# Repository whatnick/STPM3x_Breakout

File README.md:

# STPM3x Energy Metering Breakouts

Open-hardware development boards for the STMicroelectronics STPM32, STPM33,
and STPM34 energy-metering ASIC family.

The STPM3x devices combine precision analog conversion with on-chip
calculation of voltage, current, power, energy, and power-quality events. They
support current transformers, shunts, and Rogowski coils, with SPI or UART
host communication and CRC-protected data transfers.

This repository develops a consistent breakout family around all three channel
configurations:

| Board | Measurement channels | Best fit |
|---|---|---|
| **STPM32 Breakout** | 1 voltage + 1 current | Single-phase meters, smart appliances, and compact sensor development |
| **STPM33 Breakout** | 1 voltage + 2 current | Phase/neutral monitoring, tamper detection, and dual-current experiments |
| **STPM34 Breakout** | 2 voltage + 2 current | Split-phase systems, two independent circuits, and two-phase monitoring |

The STPM34 is the most capable member of this family, but it is not a complete
three-phase meter by itself. Applications requiring three simultaneous voltage
and current phases are better served by devices such as the ADE9000 or
ATM90E36.

## Place in the Whatnick ecosystem

The Whatnick energy-monitoring ecosystem includes breakout boards and drivers
for several metering architectures:

- **ATM90E26** for established single-phase SPI metering.
- **ATM90E32/ATM90E36** for three-phase monitoring.
- **ADE7763 and ADE7816** for Analog Devices single- and multi-channel designs.
- **ADE9000** for advanced polyphase metering and power-quality work.
- **CS5464 and CS5490** for Cirrus Logic single-phase applications.
- **MCP39F511 and MCP39F521** for Microchip calculation-engine devices.
- **V9203 and V93xx** for additional polyphase and single-phase platforms.
- **STPM3x** for a scalable STMicroelectronics family using a common register
  model across single-, dual-current, and dual-channel applications.

The aim is not only to expose IC pins. Each breakout should provide a known
hardware platform for driver development, calibration tools, sensor-interface
experiments, waveform analysis, and comparison between metering ASIC families.

## Intended software ecosystem

The three boards are intended to share one transport-independent STPM3x driver
core with device-specific channel capabilities layered on top. Planned software
support includes:

- Register definitions and typed configuration helpers.
- SPI and UART transports.
- CRC generation and checking.
- RMS, power, energy, event, and status access.
- Calibration and register-dump tools.
- Arduino and Python/MicroPython-facing APIs.
- Examples for CT, shunt, and Rogowski-coil measurements.

Keeping a common API across STPM32, STPM33, and STPM34 will allow applications
to move between board variants without maintaining three unrelated drivers.

## Hardware philosophy

These boards are intended as accessible bench-development platforms:

- Clearly separated analog sensor and digital host interfaces.
- Exposed pulse, interrupt, synchronization, clock, and enable signals.
- Space for channel-specific burden, divider, protection, and filtering
  networks.
- 3.3 V host compatibility.
- Compact breadboard modules or larger bench boards according to channel count.
- Readable safety labels and accessible test points.
- Open KiCad 10 source and project-local STPM3x symbols.

The STPM32 variant implements a complete compact front end for a
100 A:50 mA current-output CT and an isolated 9 VAC transformer secondary. It
uses a single 1x12 breadboard header, underside test pads, separate analog and
digital ground pours, and no field-wiring connectors. The STPM33 variant is
also complete, using the same isolated 9 VAC input with two 100 A:50 mA CT
channels, a 1x14 development header, five underside test pads, and a 55 x 40 mm
bench-board envelope. The STPM34 variant is complete on a 75 x 50 mm bench
board with two isolated 9 VAC channels, two 100 A:50 mA CT channels, separate
analog and host headers, and three underside test pads.

## Repository contents

- [`hardware/STPM32_Breakout`](hardware/STPM32_Breakout) - single voltage and
  current channel.
- [`hardware/STPM33_Breakout`](hardware/STPM33_Breakout) - single voltage and
  dual current channels.
- [`hardware/STPM34_Breakout`](hardware/STPM34_Breakout) - dual voltage and
  current channels.
- [`symbols/STPM3x.kicad_sym`](symbols/STPM3x.kicad_sym) - project-local,
  datasheet-verified symbols.
- [`docs/pin-map.md`](docs/pin-map.md) - family pin and package comparison.
- [`docs/design-requirements.md`](docs/design-requirements.md) - shared
  electrical, mechanical, and safety requirements.

## Safety

These are development boards, not certified energy meters. They must not be
connected directly to hazardous voltages without correctly rated isolation,
protection, fusing, spacing, enclosure, and appropriate electrical-safety
practices.

## License

Hardware design files are released under the
[TAPR Open Hardware License 1.0](LICENSE).

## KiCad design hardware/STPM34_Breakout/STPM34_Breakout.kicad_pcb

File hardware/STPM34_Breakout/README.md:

# STPM34 Breakout

KiCad 10 open-hardware breakout for the STMicroelectronics STPM34 metering
ASIC. It measures two isolated voltage channels and two current-transformer
channels for split-phase, dual-circuit, and two-phase development.

## Front end

- Supply: 3.3 V.
- Voltage inputs: two isolated 9 VAC transformer secondaries.
- Current inputs: two 100 A:50 mA CTs.
- Current burdens: 2.4 ohm differential, giving 120 mV RMS at 100 A.
- Current filters: 100 ohm series resistors and 330 nF capacitors.
- Voltage dividers: symmetric 200 kohm / 2.49 kohm per channel.
- Voltage filters: 1 kohm series resistors and 33 nF capacitors.
- Clock: 16 MHz crystal.
- Grounding: separate GNDA and DGND pours joined through NT1. NT1 is a copper
  net tie; no component is fitted there.

This is not an isolated mains-input board. Connect only isolated low-voltage
sources and follow applicable electrical-safety practices.

## Headers

J1 carries the analog inputs:

| Pin | Signal | Pin | Signal |
|---:|---|---:|---|
| 1 | V1AC_P | 5 | CT1_P |
| 2 | V1AC_N | 6 | CT1_N |
| 3 | V2AC_P | 7 | CT2_P |
| 4 | V2AC_N | 8 | CT2_N |

J2 carries power and the host interface:

| Pin | Signal | Pin | Signal |
|---:|---|---:|---|
| 1 | +3V3 | 6 | MISO/TXD |
| 2 | DGND | 7 | SYN |
| 3 | SCS | 8 | EN |
| 4 | SCL | 9 | INT1 |
| 5 | MOSI/RXD | 10 | INT2 |

Underside pads expose LED1, LED2, and CLKOUT/ZCR.

## SPI/UART selector

STPM34 supports SPI or UART, not I2C. SJ1 biases SCS through R14 at power-up:

- Pads 1-2 are closed by default, selecting SPI with a DGND bias.
- For UART, cut pads 1-2 and bridge pads 2-3 to bias SCS to +3V3.
- Press SW1 after changing SJ1 so EN is asserted low and the interface mode is
  sampled again.

## Rebuilding

Run the scripts from the repository root:

```powershell
python .\scripts\build_stpm34_schematic.py
python .\scripts\apply_stpm34_bom.py
& "C:\Program Files\KiCad\10.0\bin\python.exe" .\scripts\build_stpm34_pcb.py
```

Routing uses Freerouting with Java 25:

```powershell
$env:JAVA25 = "C:\Program Files\Eclipse Adoptium\jre-25.0.4.101-hotspot\bin\java.exe"
$env:FREEROUTING_JAR = "C:\path\to\freerouting-2.4.1.jar"
& "C:\Program Files\KiCad\10.0\bin\python.exe" .\scripts\route_stpm34.py
& "C:\Program Files\KiCad\10.0\bin\python.exe" .\scripts\finalize_stpm34_pcb.py
```

The checked-in routed PCB is the production source. Reconstruction scripts
capture the electrical design, 75 x 50 mm rounded envelope, placement,
routing workflow, ground pours, markings, and project-local 3D/logo assets.

## Manufacturing outputs

```powershell
python .\scripts\apply_stpm34_bom.py
python .\scripts\render_stpm34.py
python .\scripts\generate_stpm34_gerbers.py
```

The Elecrow BOM is written to `manufacturing`. Gerbers, separate PTH/NPTH
drills, Gerber job data, front/rear position CSVs, and the upload ZIP are
written to `gerber`. The BOM contains 17 grouped unique parts and 44 fitted
components.

## Breadboard bench scene

The FreeCAD and Blender scene illustrates a safe low-voltage demonstration:
an isolated 9 VAC barrel adapter feeds the voltage input and a 9 VAC lamp,
while a YHDC current-transformer clamp surrounds one lamp conductor and
connects through a stereo-jack breakout. The composition is an original
render inspired by common Whatnick bench practice and the supplied Tindie
reference photograph; it is not a literal reconstruction of that photograph.

Generate the editable FreeCAD model, intermediate STEP/OBJ geometry, Blender
scene, and final PNG from the repository root:

```powershell
& "C:\Program Files\FreeCAD 0.19\bin\FreeCADCmd.exe" .\scripts\build_stpm34_bench_freecad.py
& "C:\Program Files\Blender Foundation\Blender 5.2\blender.exe" --background --python .\scripts\render_stpm34_bench_blender.py
```

The checked-in deliverables are the `.FCStd`, `.blend`, and `.png` files.
Intermediate STEP and OBJ exports are regenerated locally and ignored by Git.

**Safety:** the scene represents an isolated 9 VAC test circuit only. Never
connect mains voltage directly to a breadboard, the STPM34 analog header, or
the rendered barrel/stereo breakout arrangement.

## Validation

KiCad 10 ERC and DRC are mandatory before fabrication export. The Gerber
generator enforces zero ERC/DRC violations and zero unconnected items before
creating the package.

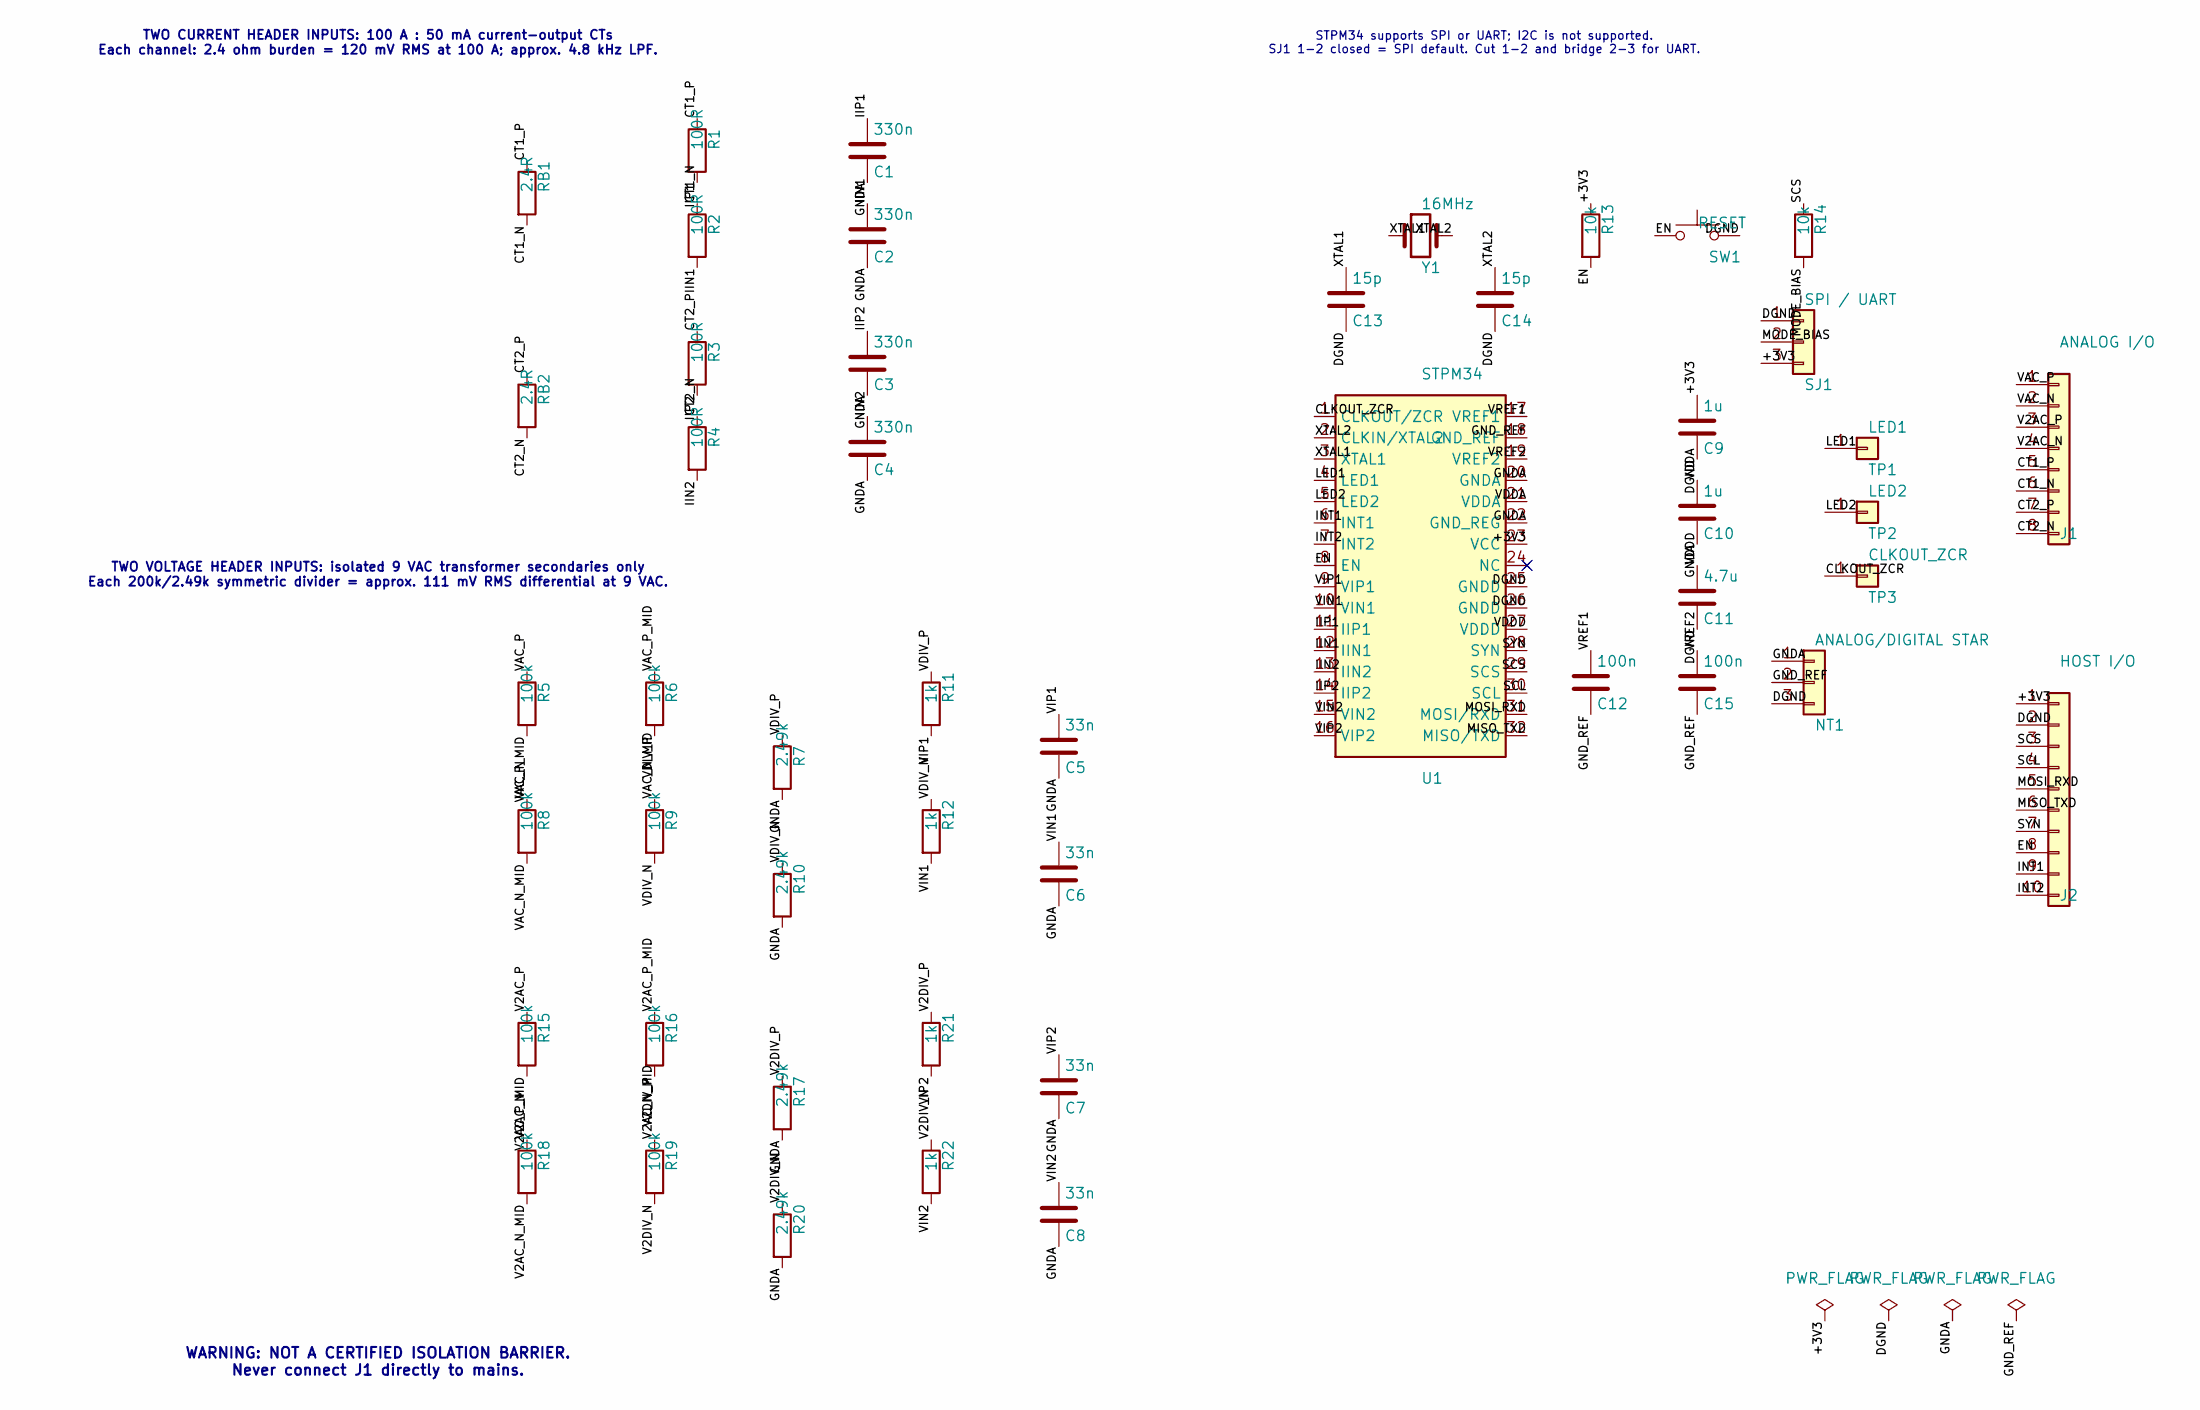
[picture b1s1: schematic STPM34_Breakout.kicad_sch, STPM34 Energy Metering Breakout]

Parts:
C1, C2, C3, C4: 330n; C_0603_1608Metric; MPN TCC0603X7R334K500CT; LCSC C282682
C5, C6, C7, C8: 33n; C_0603_1608Metric; MPN CL10B333KB8NNNC; LCSC C21117
C9, C10: 1u; C_0805_2012Metric; MPN CL21B105KAFNNNE; LCSC C116352
C11: 4.7u; C_0805_2012Metric; MPN CL21A475KOFNNNG; LCSC C16194928
C12, C15: 100n; C_0603_1608Metric; MPN CL10B104KB8NNNC; LCSC C1591
C13, C14: 15p; C_0603_1608Metric; MPN CL10C150JB8NNNC; LCSC C1644
J1: ANALOG I/O; PinHeader_1x08_P2.54mm_Vertical; MPN PZ254V-11-08P; LCSC C492407
J2: HOST I/O; PinHeader_1x10_P2.54mm_Vertical; MPN PZ254V-11-10P; LCSC C492409
NT1: ANALOG/DIGITAL STAR; NetTie-3_SMD_Pad0.5mm
R1, R2, R3, R4: 100R; R_0603_1608Metric; MPN RC0603FR-07100RL; LCSC C105588
R5, R6, R8, R9, R15, R16, R18, R19: 100k; R_0603_1608Metric; MPN RT0603BRD07100KL; LCSC C122538
R7, R10, R17, R20: 2.49k; R_0603_1608Metric; MPN RT0603BRD072K49L; LCSC C861299
R11, R12, R21, R22: 1k; R_0603_1608Metric; MPN RC0603FR-071KL; LCSC C22548
R13, R14: 10k; R_0603_1608Metric; MPN RC0603FR-0710KL; LCSC C98220
RB1, RB2: 2.4R; R_0603_1608Metric; MPN RC0603FR-072R4L; LCSC C137746
SJ1: SPI / UART; SolderJumper-3_P1.3mm_Bridged12_Pad1.0x1.5mm
SW1: RESET; SW_SPST_CK_RS282G05A3; MPN RS-282G05A3-SMRT; LCSC C221930
TP1: LED1; TestPoint_Pad_D1.5mm
TP2: LED2; TestPoint_Pad_D1.5mm
TP3: CLKOUT_ZCR; TestPoint_Pad_D1.5mm
U1: STPM34; QFN-32-1EP_5x5mm_P0.5mm_EP3.45x3.45mm; MPN STPM34TR; LCSC C129475
Y1: 16MHz; Crystal_SMD_3225-4Pin_3.2x2.5mm; MPN X322516MOB4SI; LCSC C12668

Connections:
+3V3: C9.1, J2.1, R13.1, SJ1.3, U1.23 (VCC)
CLKOUT_ZCR: TP3.1, U1.1 (CLKOUT/ZCR)
CT1_N: J1.6, R2.1, RB1.2
CT1_P: J1.5, R1.1, RB1.1
CT2_N: J1.8, R4.1, RB2.2
CT2_P: J1.7, R3.1, RB2.1
DGND: C9.2, C11.2, C13.2, C14.2, J2.2, NT1.3, SJ1.1, SW1.2, U1.25 (GNDD), U1.26 (GNDD)
EN: J2.8, R13.2, SW1.1, U1.8 (EN)
GNDA: C1.2, C2.2, C3.2, C4.2, C5.2, C6.2, C7.2, C8.2, C10.2, NT1.1, R7.2, R10.2, R17.2, R20.2, U1.20 (GNDA), U1.22 (GND_REG)
GND_REF: C12.2, C15.2, NT1.2, U1.18 (GND_REF)
IIN1: C2.1, R2.2, U1.12 (IIN1)
IIN2: C4.1, R4.2, U1.13 (IIN2)
IIP1: C1.1, R1.2, U1.11 (IIP1)
IIP2: C3.1, R3.2, U1.14 (IIP2)
INT1: J2.9, U1.6 (INT1)
INT2: J2.10, U1.7 (INT2)
LED1: TP1.1, U1.4 (LED1)
LED2: TP2.1, U1.5 (LED2)
MISO_TXD: J2.6, U1.32 (MISO/TXD)
MODE_BIAS: R14.2, SJ1.2
MOSI_RXD: J2.5, U1.31 (MOSI/RXD)
SCL: J2.4, U1.30 (SCL)
SCS: J2.3, R14.1, U1.29 (SCS)
SYN: J2.7, U1.28 (SYN)
V2AC_N: J1.4, R18.1
V2AC_N_MID: R18.2, R19.1
V2AC_P: J1.3, R15.1
V2AC_P_MID: R15.2, R16.1
V2DIV_N: R19.2, R20.1, R22.1
V2DIV_P: R16.2, R17.1, R21.1
VAC_N: J1.2, R8.1
VAC_N_MID: R8.2, R9.1
VAC_P: J1.1, R5.1
VAC_P_MID: R5.2, R6.1
VDDA: C10.1, U1.21 (VDDA)
VDDD: C11.1, U1.27 (VDDD)
VDIV_N: R9.2, R10.1, R12.1
VDIV_P: R6.2, R7.1, R11.1
VIN1: C6.1, R12.2, U1.10 (VIN1)
VIN2: C8.1, R22.2, U1.15 (VIN2)
VIP1: C5.1, R11.2, U1.9 (VIP1)
VIP2: C7.1, R21.2, U1.16 (VIP2)
VREF1: C12.1, U1.17 (VREF1)
VREF2: C15.1, U1.19 (VREF2)
XTAL1: C13.1, U1.3 (XTAL1), Y1.1
XTAL2: C14.1, U1.2 (CLKIN/XTAL2), Y1.2

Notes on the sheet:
TWO CURRENT HEADER INPUTS: 100 A : 50 mA current-output CTs Each channel: 2.4 ohm burden = 120 mV RMS at 100 A; approx. 4.8 kHz LPF.
TWO VOLTAGE HEADER INPUTS: isolated 9 VAC transformer secondaries only Each 200k/2.49k symmetric divider = approx. 111 mV RMS differential at 9 VAC.
WARNING: NOT A CERTIFIED ISOLATION BARRIER. Never connect J1 directly to mains.
STPM34 supports SPI or UART; I2C is not supported. SJ1 1-2 closed = SPI default. Cut 1-2 and bridge 2-3 for UART.

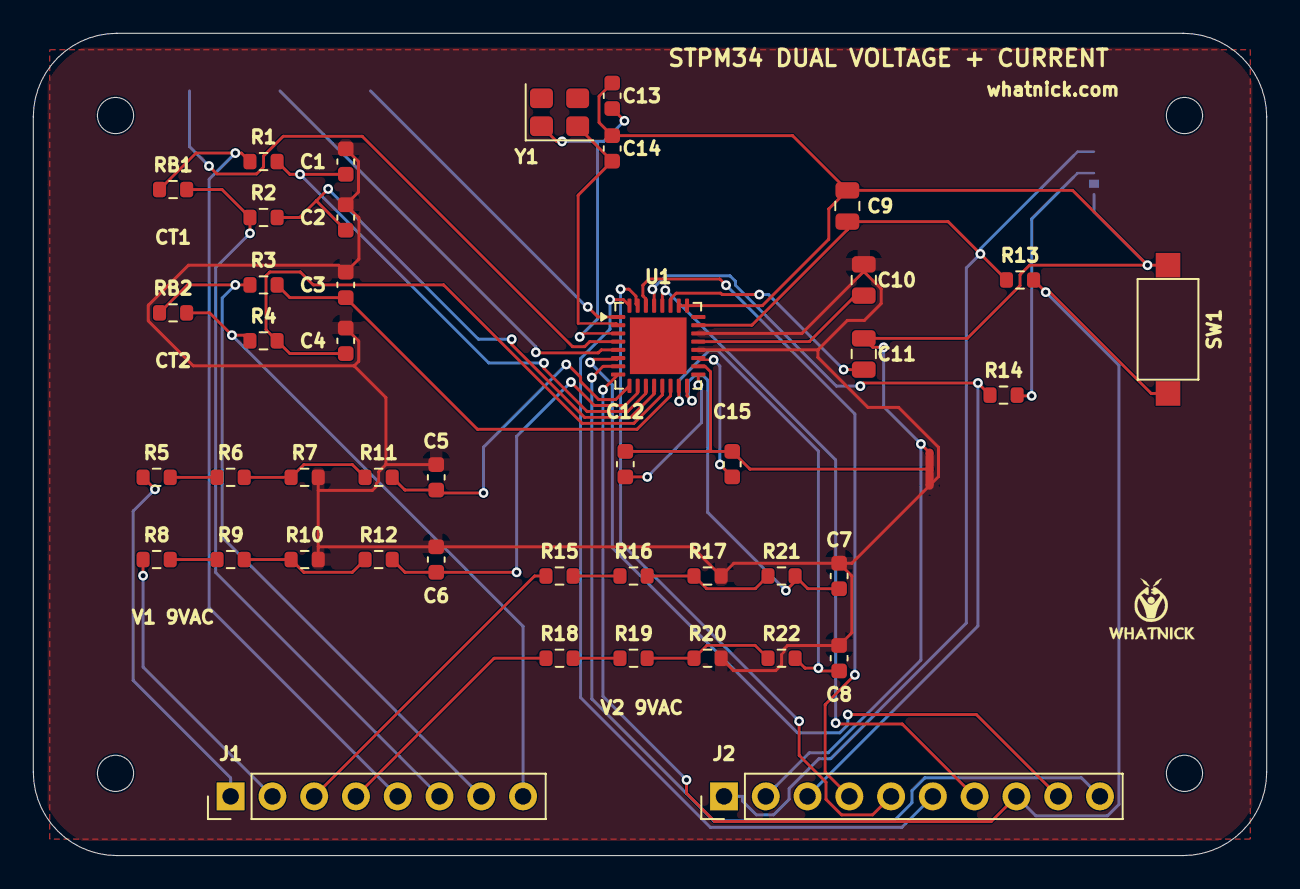
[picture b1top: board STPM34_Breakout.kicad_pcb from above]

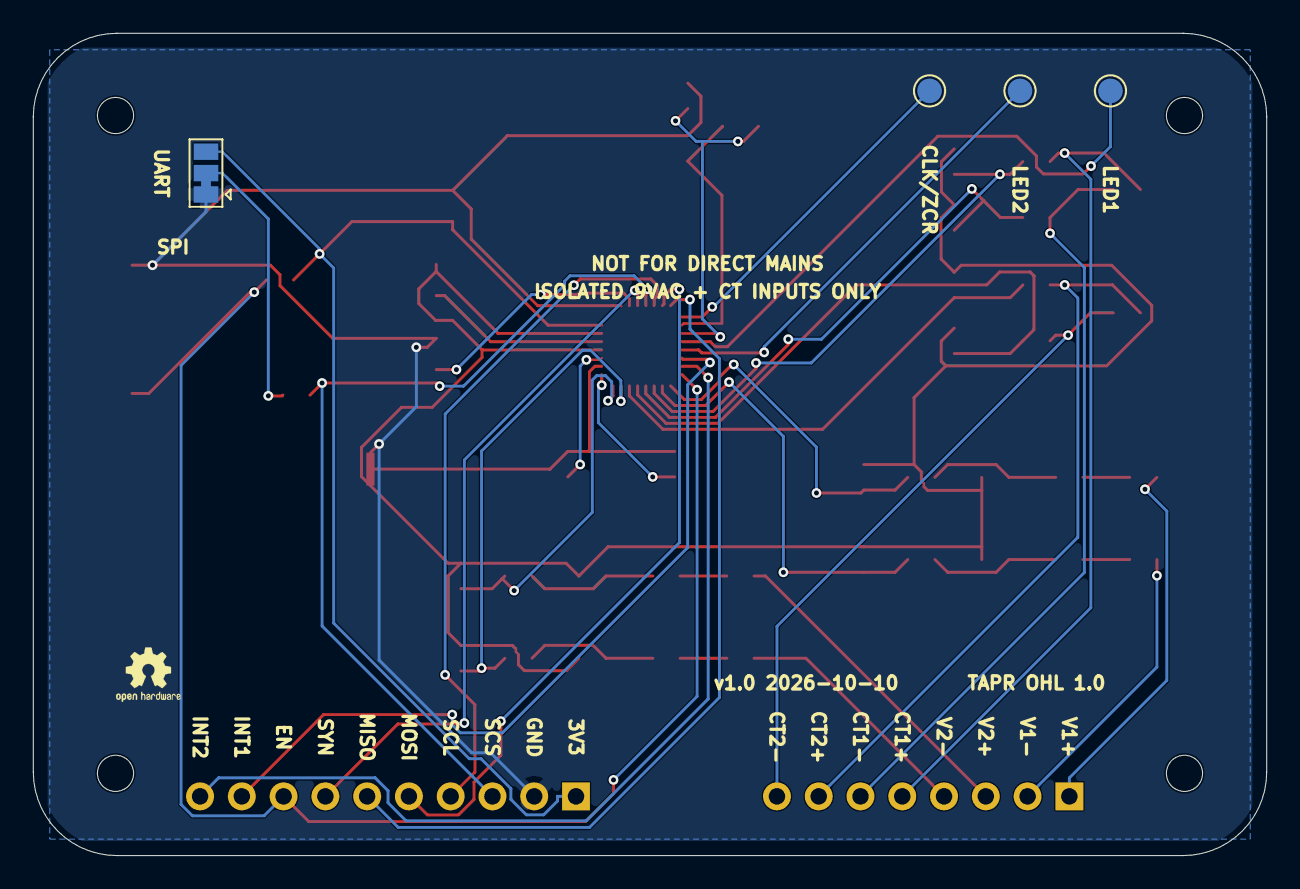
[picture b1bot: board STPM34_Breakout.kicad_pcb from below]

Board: 2 copper layers, 75.0 x 50.0 mm, 55 parts (5 on the bottom side), 46 nets.

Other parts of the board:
H1, H2, H3, H4: MountingHole_2.2mm_M2
LOGO_OSHW: OSHW_Logo
LOGO_W: Whatnick_Logo

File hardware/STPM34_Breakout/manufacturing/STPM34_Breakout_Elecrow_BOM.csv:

Reference Designator,Quantity,Manufacturer,Manufacturer Part Number,Description / Value,Package / Footprint,LCSC Part Number,Assembly Type,Purchase URL,DigiKey,Mouser,Notes
U1,1,STMicroelectronics,STPM34TR,"Dual-voltage, dual-current-channel energy-metering ASIC","QFN-32-EP, 5 x 5 mm, 0.5 mm pitch; Package_DFN_QFN:QFN-32-1EP_5x5mm_P0.5mm_EP3.45x3.45mm",C129475,SMT,https://www.lcsc.com/product-detail/C129475.html,https://www.digikey.com/en/products/result?keywords=STPM34TR,https://www.mouser.com/c/?q=STPM34TR,Inspect exposed-pad paste and voiding during DFM review.
"R1,R2,R3,R4",4,YAGEO,RC0603FR-07100RL,"100 ohm, 1%, 0.1 W thick-film resistor",0603 (1608 Metric); Resistor_SMD:R_0603_1608Metric,C105588,SMT,https://www.lcsc.com/product-detail/C105588.html,https://www.digikey.com/en/products/result?keywords=RC0603FR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,https://www.mouser.com/c/?q=RC0603FR-07100RL,
"R5,R6,R8,R9,R15,R16,R18,R19",8,YAGEO,RT0603BRD07100KL,"100 kohm, 0.1%, 25 ppm/C thin-film resistor",0603 (1608 Metric); Resistor_SMD:R_0603_1608Metric,C122538,SMT,https://www.lcsc.com/product-detail/C122538.html,https://www.digikey.com/en/products/result?keywords=RT0603BR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,https://www.mouser.com/c/?q=RT0603BRD07100KL,Use one lot for all eight voltage-divider resistors.
"R7,R10,R17,R20",4,YAGEO,RT0603BRD072K49L,"2.49 kohm, 0.1%, 25 ppm/C thin-film resistor",0603 (1608 Metric); Resistor_SMD:R_0603_1608Metric,C861299,SMT,https://www.lcsc.com/product-detail/C861299.html,https://www.digikey.com/en/products/result?keywords=RT0603BR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,https://www.mouser.com/c/?q=RT0603BRD072K49L,Use one lot for all four matched voltage-divider low sides.
"R11,R12,R21,R22",4,YAGEO,RC0603FR-071KL,"1 kohm, 1%, 0.1 W thick-film resistor",0603 (1608 Metric); Resistor_SMD:R_0603_1608Metric,C22548,SMT,https://www.lcsc.com/product-detail/C22548.html,https://www.digikey.com/en/products/result?keywords=RC0603FR-071KL,https://www.mouser.com/c/?q=RC0603FR-071KL,
"R13,R14",2,YAGEO,RC0603FR-0710KL,"10 kohm, 1%, 0.1 W thick-film resistor",0603 (1608 Metric); Resistor_SMD:R_0603_1608Metric,C98220,SMT,https://www.lcsc.com/product-detail/C98220.html,https://www.digikey.com/en/products/result?keywords=RC0603FR-0710KL,https://www.mouser.com/c/?q=RC0603FR-0710KL,
"RB1,RB2",2,YAGEO,RC0603FR-072R4L,"2.4 ohm, 1%, 0.1 W CT burden resistor",0603 (1608 Metric); Resistor_SMD:R_0603_1608Metric,C137746,SMT,https://www.lcsc.com/product-detail/C137746.html,https://www.digikey.com/en/products/result?keywords=RC0603FR-072R4L,https://www.mouser.com/c/?q=RC0603FR-072R4L,About 6 mW at 50 mA RMS. The 200 ppm/C TCR is suitable for development; use a lower-TCR burden for calibration-grade builds.
"C1,C2,C3,C4",4,CCTC,TCC0603X7R334K500CT,"330 nF, 50 V, 10%, X7R MLCC",0603 (1608 Metric); Capacitor_SMD:C_0603_1608Metric,C282682,SMT,https://www.lcsc.com/product-detail/C282682.html,https://www.digikey.com/en/products/result?keywords=TCC0603X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,https://www.mouser.com/c/?q=TCC0603X7R334K500CT,
"C5,C6,C7,C8",4,Samsung Electro-Mechanics,CL10B333KB8NNNC,"33 nF, 50 V, 10%, X7R MLCC",0603 (1608 Metric); Capacitor_SMD:C_0603_1608Metric,C21117,SMT,https://www.lcsc.com/product-detail/C21117.html,https://www.digikey.com/en/products/result?keywords=CL10B333KB8NNNC,https://www.mouser.com/c/?q=CL10B333KB8NNNC,
"C12,C15",2,Samsung Electro-Mechanics,CL10B104KB8NNNC,"100 nF, 50 V, 10%, X7R MLCC",0603 (1608 Metric); Capacitor_SMD:C_0603_1608Metric,C1591,SMT,https://www.lcsc.com/product-detail/C1591.html,https://www.digikey.com/en/products/result?keywords=CL10B104KB8NNNC,https://www.mouser.com/c/?q=CL10B104KB8NNNC,
"C13,C14",2,Samsung Electro-Mechanics,CL10C150JB8NNNC,"15 pF, 50 V, 5%, C0G MLCC",0603 (1608 Metric); Capacitor_SMD:C_0603_1608Metric,C1644,SMT,https://www.lcsc.com/product-detail/C1644.html,https://www.digikey.com/en/products/result?keywords=CL10C150JB8NNNC,https://www.mouser.com/c/?q=CL10C150JB8NNNC,
"C9,C10",2,Samsung Electro-Mechanics,CL21B105KAFNNNE,"1 uF, 25 V, 10%, X7R MLCC",0805 (2012 Metric); Capacitor_SMD:C_0805_2012Metric,C116352,SMT,https://www.lcsc.com/product-detail/C116352.html,https://www.digikey.com/en/products/result?keywords=CL21B105KAFNNNE,https://www.mouser.com/c/?q=CL21B105KAFNNNE,
C11,1,Samsung Electro-Mechanics,CL21A475KOFNNNG,"4.7 uF, 16 V, 10%, X5R MLCC",0805 (2012 Metric); Capacitor_SMD:C_0805_2012Metric,C16194928,SMT,https://www.lcsc.com/product-detail/C16194928.html,https://www.digikey.com/en/products/result?keywords=CL21A475KOFNNNG,https://www.mouser.com/c/?q=CL21A475KOFNNNG,
Y1,1,YXC,X322516MOB4SI,"16 MHz, 12 pF load crystal",SMD3225-4P; Crystal:Crystal_SMD_3225-4Pin_3.2x2.5mm,C12668,SMT,https://www.lcsc.com/product-detail/C12668.html,https://www.digikey.com/en/products/result?keywords=X322516MOB4SI,https://www.mouser.com/c/?q=X322516MOB4SI,12 pF load is consistent with two 15 pF capacitors plus estimated pin and PCB stray capacitance; verify oscillator margin on prototypes.
SW1,1,C&K,RS-282G05A3-SMRT,Momentary SPST reset switch,C&K RS-282G05A3 SMD; Button_Switch_SMD:SW_SPST_CK_RS282G05A3,C221930,SMT,https://www.lcsc.com/product-detail/C221930.html,https://www.digikey.com/en/products/result?keywords=RS-282G0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,https://www.mouser.com/c/?q=RS-282G05A3-SMRT,
J1,1,XFCN,PZ254V-11-08P,Single-row analog-input male pin header,"1x8, 2.54 mm pitch, vertical THT; Connector_PinHeader_2.54mm:PinHeader_1x08_P2.54mm_Vertical",C492407,THT,https://www.lcsc.com/product-detail/C492407.html,https://www.digikey.com/en/products/result?keywords=PZ254V-11-08P,https://www.mouser.com/c/?q=PZ254V-11-08P,Quote THT assembly separately and confirm pin protrusion suits breadboards.
J2,1,XFCN,PZ254V-11-10P,Single-row host-interface male pin header,"1x10, 2.54 mm pitch, vertical THT; Connector_PinHeader_2.54mm:PinHeader_1x10_P2.54mm_Vertical",C492409,THT,https://www.lcsc.com/product-detail/C492409.html,https://www.digikey.com/en/products/result?keywords=PZ254V-11-10P,https://www.mouser.com/c/?q=PZ254V-11-10P,Quote THT assembly separately and confirm mating header geometry.

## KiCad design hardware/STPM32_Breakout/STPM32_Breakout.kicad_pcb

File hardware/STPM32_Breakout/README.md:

# STPM32 breakout

Compact KiCad 10 development board for the single-voltage, single-current
STMicroelectronics STPM32 energy-metering ASIC.

## 3D renders

## Implemented front end

- **Current input:** 100 A:50 mA current-output CT.
- **Burden:** 2.4 ohm differential, producing 120 mV RMS at 100 A.
- **Current filter:** 100 ohm series and 330 nF shunt on each differential leg,
  approximately 4.8 kHz.
- **Voltage input:** isolated 9 VAC transformer secondary.
- **Voltage divider:** 200 kohm / 2.49 kohm on each conductor, approximately
  81.3:1 differential scaling.
- **Voltage filter:** 1 kohm series and 33 nF shunt on each differential leg,
  approximately 4.8 kHz.
- **Clock:** 16 MHz crystal with 15 pF load capacitors.
- **Interface selector:** STPM32 supports SPI and UART, not I2C. SJ1 is a
  three-pad solder jumper with pads 1-2 closed by default, weakly pulling SCS
  low through R12 for SPI. For UART, cut the 1-2 bridge and solder 2-3 so R12
  weakly pulls SCS high. The resistor preserves host control of SCS in SPI mode.

At 9 VAC differential input, the voltage channel receives approximately
111 mV RMS, or 157 mV peak. Both analog channels remain below the STPM32
maximum differential input of +/-300 mV at their stated full-scale inputs.

## Breadboard header

| Pin | Signal | Pin | Signal |
|---:|---|---:|---|
| 1 | +3V3 | 7 | SCS |
| 2 | DGND | 8 | SCL |
| 3 | VAC_P | 9 | MOSI/RXD |
| 4 | VAC_N | 10 | MISO/TXD |
| 5 | CT_P | 11 | SYN |
| 6 | CT_N | 12 | EN |

INT1, LED1, LED2, and CLKOUT/ZCR are available on underside test pads.

## Mechanical and validation status

- 38.2 x 28.04 mm rounded board.
- Single long-edge 1x12, 2.54 mm header.
- No screw terminals, audio jacks, or direct-mains connector.
- Routed two-layer PCB with separate AGND and DGND pours joined through the
  three-pad analog/reference/digital ground net tie.
- Production silkscreen uses 0.8 x 0.8 mm component and signal labels with
  0.2 mm stroke, project-local Whatnick and OSHW logos, and explicit revision
  and build-date marking.
- U1 uses the project-local
  `models/step/STPM32_VQFN24_4x4_EP2.45.step` model. It matches the 4 x 4 mm,
  1.0 mm-high, 0.5 mm-pitch VQFN-24 envelope and nominal 2.45 x 2.45 mm
  exposed pad instead of relying on the missing similarly named KiCad library
  model. Geometry and orientation were cross-checked against ST's
  `STPM32.STEP` vendor model dated 2024-01-25; the vendor file is not
  redistributed.
- ERC: zero violations.
- DRC: zero violations and zero unconnected pads.

Regenerate the model and committed renders with:

```powershell
python -m pip install cadquery
python .\scripts\create_stpm32_qfn_step.py
python .\scripts\render_stpm32.py
```

## Gerber fabrication package

Generate the KiCad 10 fabrication outputs with:

```powershell
python .\scripts\generate_stpm32_gerbers.py
```

The script runs ERC and DRC before exporting the two copper layers, solder
masks, front and rear silkscreens, front paste, board outline, separate
plated/non-plated Excellon drill files, and front/rear component position CSV
files. Outputs are written to:

- `hardware/STPM32_Breakout/gerber/`
- `hardware/STPM32_Breakout/gerber/STPM32_Breakout_Gerbers.zip`

Upload the ZIP through Elecrow's PCB manufacturing web form. Elecrow does not
currently document a public PCB order or Gerber-upload API, so no account
credentials are required by this repository.

## Elecrow assembly BOM

The initial production selection uses exact manufacturer part numbers and LCSC
catalog identifiers so Elecrow can quote turnkey sourcing without substituting
parts from value-only descriptions. Precision 0.1%, 25 ppm/C resistors are
specified for the voltage-divider ratios; the remaining resistors are 1%.
Filter capacitors use X7R dielectric, crystal load capacitors use C0G, and the
16 MHz crystal is specified for 12 pF load capacitance. The selected 2.4 ohm
burden is suitable for development builds; use a lower-TCR burden selection
before claiming calibration-grade temperature stability.

Apply the sourcing metadata and regenerate the quote BOM with:

```powershell
python .\scripts\apply_stpm32_bom.py
```

The generated file is:

- `manufacturing/STPM32_Breakout_Elecrow_BOM.csv`

Assembly notes:

- U1 and all other SMT parts are intended for Elecrow placement.
- J1 is the only THT line and should be quoted separately; confirm that the
  fitted pin protrusion is suitable for breadboard use.
- TP1-TP4 and NT1 are PCB features, not purchasable components, and are
  excluded from the schematic BOM and placement outputs.
- Whatnick and OSHW logo footprints are excluded from BOM and placement files.
- Verify live stock, pricing, and approved substitutions when requesting each
  production quote.

## Safety

The voltage input is for an isolated 9 VAC transformer secondary only. This
development board is not a certified isolation barrier and must never be
connected directly to mains.

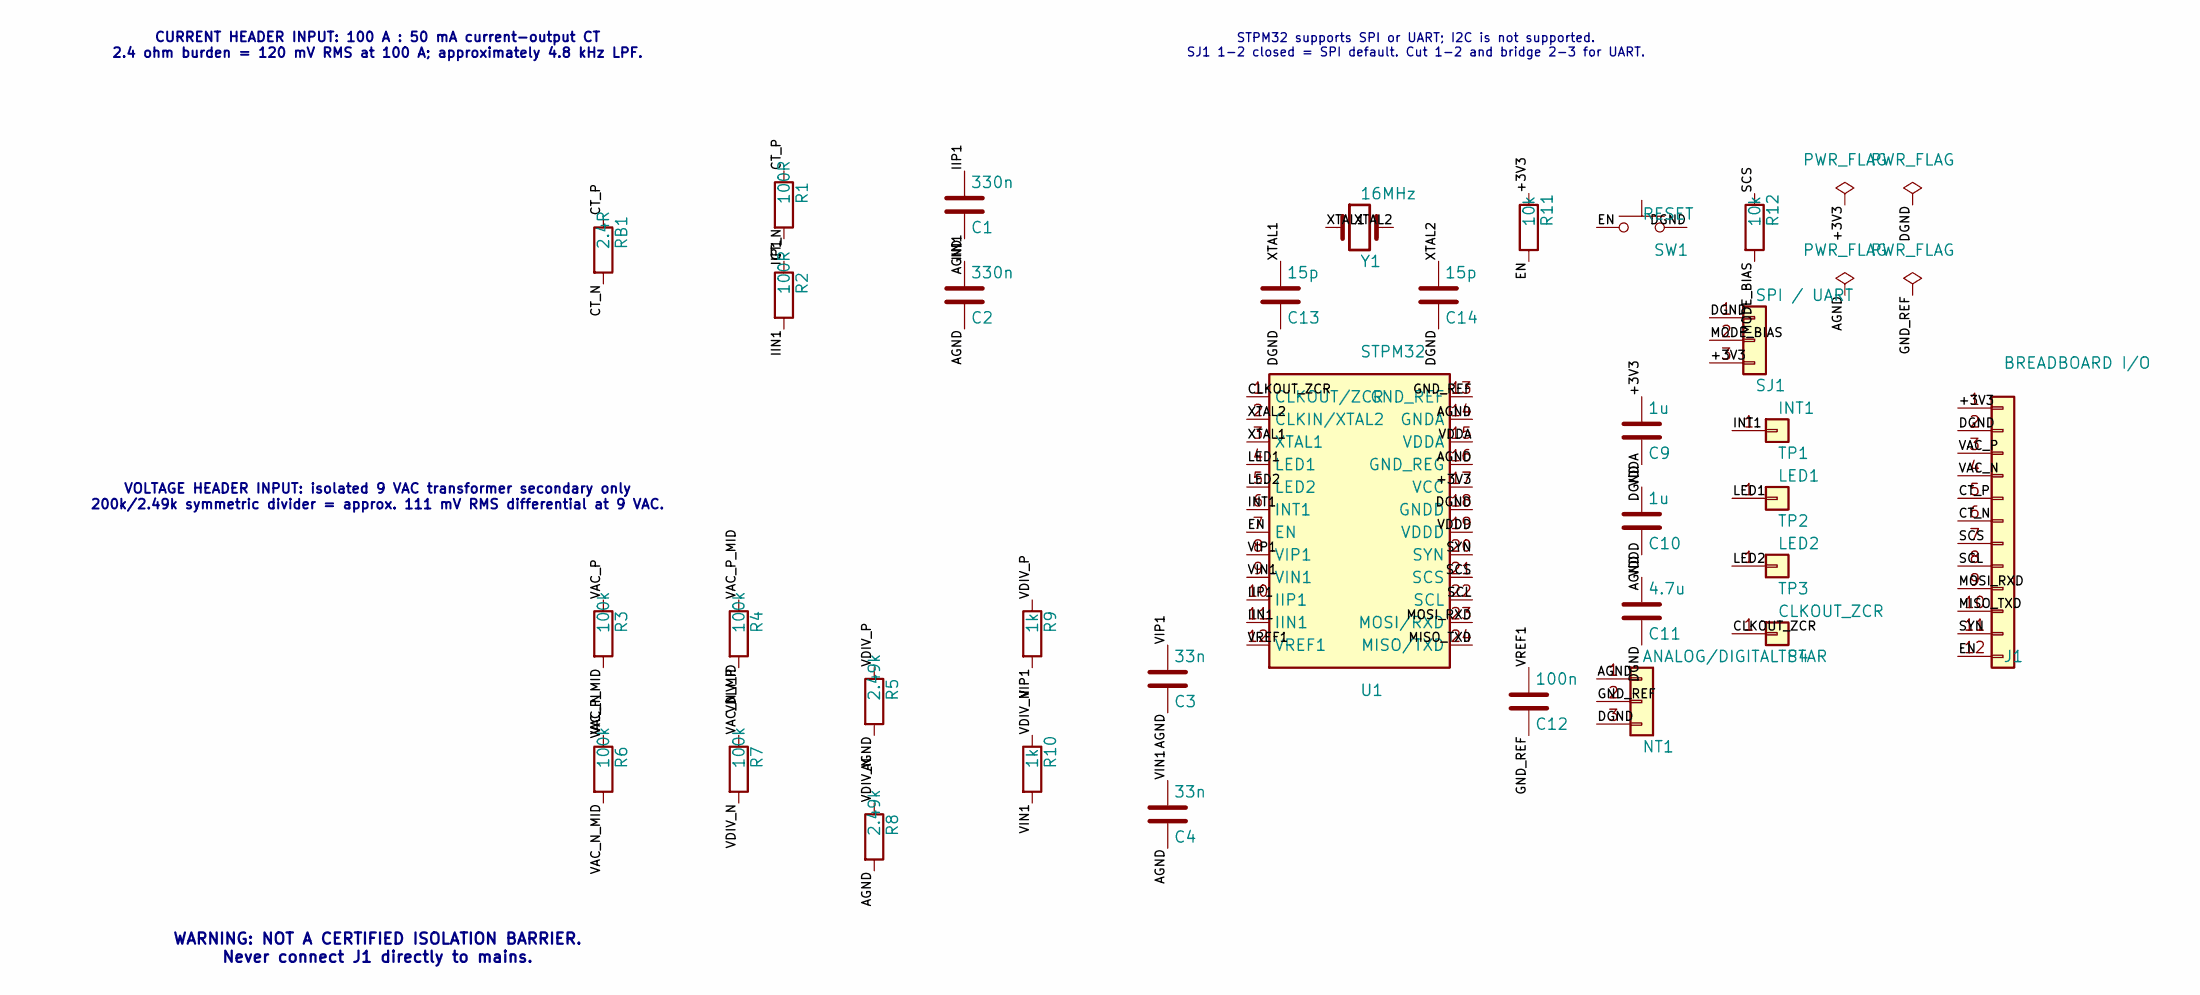
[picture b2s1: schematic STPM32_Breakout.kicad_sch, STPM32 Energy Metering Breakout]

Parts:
C1, C2: 330n; C_0603_1608Metric; MPN TCC0603X7R334K500CT; LCSC C282682
C3, C4: 33n; C_0603_1608Metric; MPN CL10B333KB8NNNC; LCSC C21117
C9, C10: 1u; C_0805_2012Metric; MPN CL21B105KAFNNNE; LCSC C116352
C11: 4.7u; C_0805_2012Metric; MPN CL21A475KOFNNNG; LCSC C16194928
C12: 100n; C_0603_1608Metric; MPN CL10B104KB8NNNC; LCSC C1591
C13, C14: 15p; C_0603_1608Metric; MPN CL10C150JB8NNNC; LCSC C1644
J1: BREADBOARD I/O; PinHeader_1x12_P2.54mm_Vertical; MPN PZ254V-11-12P; LCSC C2840012
NT1: ANALOG/DIGITAL STAR; NetTie-3_SMD_Pad0.5mm
R1, R2: 100R; R_0603_1608Metric; MPN RC0603FR-07100RL; LCSC C105588
R3, R4, R6, R7: 100k; R_0603_1608Metric; MPN RT0603BRD07100KL; LCSC C122538
R5, R8: 2.49k; R_0603_1608Metric; MPN RT0603BRD072K49L; LCSC C861299
R9, R10: 1k; R_0603_1608Metric; MPN RC0603FR-071KL; LCSC C22548
R11, R12: 10k; R_0603_1608Metric; MPN RC0603FR-0710KL; LCSC C98220
RB1: 2.4R; R_0603_1608Metric; MPN RC0603FR-072R4L; LCSC C137746
SJ1: SPI / UART; SolderJumper-3_P1.3mm_Bridged12_Pad1.0x1.5mm
SW1: RESET; SW_SPST_CK_RS282G05A3; MPN RS-282G05A3-SMRT; LCSC C221930
TP1: INT1; TestPoint_Pad_D1.5mm
TP2: LED1; TestPoint_Pad_D1.5mm
TP3: LED2; TestPoint_Pad_D1.5mm
TP4: CLKOUT_ZCR; TestPoint_Pad_D1.5mm
U1: STPM32; VQFN-24-1EP_4x4mm_P0.5mm_EP2.45x2.45mm; MPN STPM32TR; LCSC C128380
Y1: 16MHz; Crystal_SMD_3225-4Pin_3.2x2.5mm; MPN X322516MOB4SI; LCSC C12668

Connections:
+3V3: C9.1, J1.1, R11.1, SJ1.3, U1.17 (VCC)
AGND: C1.2, C2.2, C3.2, C4.2, C10.2, NT1.1, R5.2, R8.2, U1.14 (GNDA), U1.16 (GND_REG)
CLKOUT_ZCR: TP4.1, U1.1 (CLKOUT/ZCR)
CT_N: J1.6, R2.1, RB1.2
CT_P: J1.5, R1.1, RB1.1
DGND: C9.2, C11.2, C13.2, C14.2, J1.2, NT1.3, SJ1.1, SW1.2, U1.18 (GNDD)
EN: J1.12, R11.2, SW1.1, U1.7 (EN)
GND_REF: C12.2, NT1.2, U1.13 (GND_REF)
IIN1: C2.1, R2.2, U1.11 (IIN1)
IIP1: C1.1, R1.2, U1.10 (IIP1)
INT1: TP1.1, U1.6 (INT1)
LED1: TP2.1, U1.4 (LED1)
LED2: TP3.1, U1.5 (LED2)
MISO_TXD: J1.10, U1.24 (MISO/TXD)
MODE_BIAS: R12.2, SJ1.2
MOSI_RXD: J1.9, U1.23 (MOSI/RXD)
SCL: J1.8, U1.22 (SCL)
SCS: J1.7, R12.1, U1.21 (SCS)
SYN: J1.11, U1.20 (SYN)
VAC_N: J1.4, R6.1
VAC_N_MID: R6.2, R7.1
VAC_P: J1.3, R3.1
VAC_P_MID: R3.2, R4.1
VDDA: C10.1, U1.15 (VDDA)
VDDD: C11.1, U1.19 (VDDD)
VDIV_N: R7.2, R8.1, R10.1
VDIV_P: R4.2, R5.1, R9.1
VIN1: C4.1, R10.2, U1.9 (VIN1)
VIP1: C3.1, R9.2, U1.8 (VIP1)
VREF1: C12.1, U1.12 (VREF1)
XTAL1: C13.1, U1.3 (XTAL1), Y1.1
XTAL2: C14.1, U1.2 (CLKIN/XTAL2), Y1.2

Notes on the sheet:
CURRENT HEADER INPUT: 100 A : 50 mA current-output CT 2.4 ohm burden = 120 mV RMS at 100 A; approximately 4.8 kHz LPF.
VOLTAGE HEADER INPUT: isolated 9 VAC transformer secondary only 200k/2.49k symmetric divider = approx. 111 mV RMS differential at 9 VAC.
WARNING: NOT A CERTIFIED ISOLATION BARRIER. Never connect J1 directly to mains.
STPM32 supports SPI or UART; I2C is not supported. SJ1 1-2 closed = SPI default. Cut 1-2 and bridge 2-3 for UART.

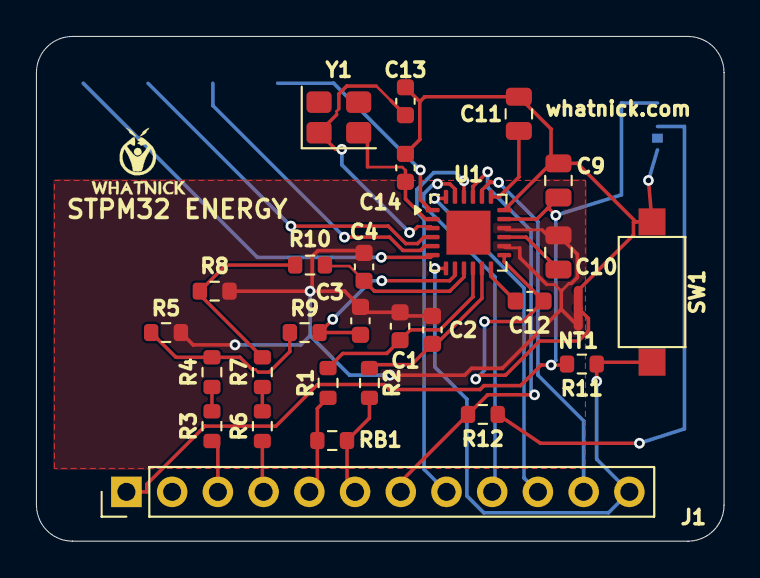
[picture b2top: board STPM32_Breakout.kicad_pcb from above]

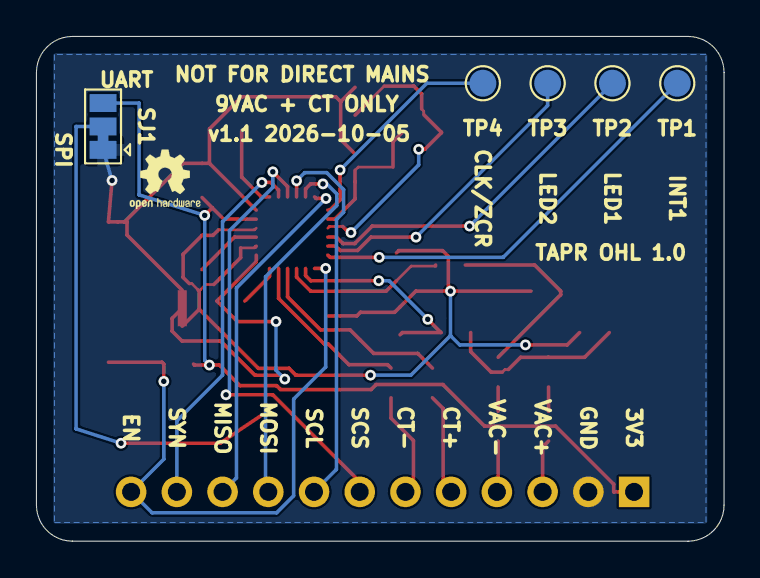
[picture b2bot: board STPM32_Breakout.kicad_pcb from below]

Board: 2 copper layers, 38.2 x 28.0 mm, 35 parts (6 on the bottom side), 32 nets.

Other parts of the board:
LOGO_OSHW: OSHW_Logo
LOGO_W: Whatnick_Logo

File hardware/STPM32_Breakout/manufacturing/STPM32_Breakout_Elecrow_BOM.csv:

Reference Designator,Quantity,Manufacturer,Manufacturer Part Number,Description / Value,Package / Footprint,LCSC Part Number,Assembly Type,Purchase URL,Notes
U1,1,STMicroelectronics,STPM32TR,Single-phase energy-metering ASIC,"VQFN-24-EP, 4 x 4 mm, 0.5 mm pitch; Package_DFN_QFN:VQFN-24-1EP_4x4mm_P0.5mm_EP2.45x2.45mm",C128380,SMT,https://www.lcsc.com/product-detail/C128380.html,Inspect exposed-pad paste and voiding during DFM review.
"R1,R2",2,YAGEO,RC0603FR-07100RL,"100 ohm, 1%, 0.1 W thick-film resistor",0603 (1608 Metric); Resistor_SMD:R_0603_1608Metric,C105588,SMT,https://www.lcsc.com/product-detail/C105588.html,
"R3,R4,R6,R7",4,YAGEO,RT0603BRD07100KL,"100 kohm, 0.1%, 25 ppm/C thin-film resistor",0603 (1608 Metric); Resistor_SMD:R_0603_1608Metric,C122538,SMT,https://www.lcsc.com/product-detail/C122538.html,Use one lot for all four voltage-divider resistors.
"R5,R8",2,YAGEO,RT0603BRD072K49L,"2.49 kohm, 0.1%, 25 ppm/C thin-film resistor",0603 (1608 Metric); Resistor_SMD:R_0603_1608Metric,C861299,SMT,https://www.lcsc.com/product-detail/C861299.html,Use one lot for the matched voltage-divider low sides.
"R9,R10",2,YAGEO,RC0603FR-071KL,"1 kohm, 1%, 0.1 W thick-film resistor",0603 (1608 Metric); Resistor_SMD:R_0603_1608Metric,C22548,SMT,https://www.lcsc.com/product-detail/C22548.html,
"R11,R12",2,YAGEO,RC0603FR-0710KL,"10 kohm, 1%, 0.1 W thick-film resistor",0603 (1608 Metric); Resistor_SMD:R_0603_1608Metric,C98220,SMT,https://www.lcsc.com/product-detail/C98220.html,
RB1,1,YAGEO,RC0603FR-072R4L,"2.4 ohm, 1%, 0.1 W CT burden resistor",0603 (1608 Metric); Resistor_SMD:R_0603_1608Metric,C137746,SMT,https://www.lcsc.com/product-detail/C137746.html,About 6 mW at 50 mA RMS. The 200 ppm/C TCR is suitable for development; use a lower-TCR burden for calibration-grade builds.
"C1,C2",2,CCTC,TCC0603X7R334K500CT,"330 nF, 50 V, 10%, X7R MLCC",0603 (1608 Metric); Capacitor_SMD:C_0603_1608Metric,C282682,SMT,https://www.lcsc.com/product-detail/C282682.html,
"C3,C4",2,Samsung Electro-Mechanics,CL10B333KB8NNNC,"33 nF, 50 V, 10%, X7R MLCC",0603 (1608 Metric); Capacitor_SMD:C_0603_1608Metric,C21117,SMT,https://www.lcsc.com/product-detail/C21117.html,
C12,1,Samsung Electro-Mechanics,CL10B104KB8NNNC,"100 nF, 50 V, 10%, X7R MLCC",0603 (1608 Metric); Capacitor_SMD:C_0603_1608Metric,C1591,SMT,https://www.lcsc.com/product-detail/C1591.html,
"C13,C14",2,Samsung Electro-Mechanics,CL10C150JB8NNNC,"15 pF, 50 V, 5%, C0G MLCC",0603 (1608 Metric); Capacitor_SMD:C_0603_1608Metric,C1644,SMT,https://www.lcsc.com/product-detail/C1644.html,
"C9,C10",2,Samsung Electro-Mechanics,CL21B105KAFNNNE,"1 uF, 25 V, 10%, X7R MLCC",0805 (2012 Metric); Capacitor_SMD:C_0805_2012Metric,C116352,SMT,https://www.lcsc.com/product-detail/C116352.html,
C11,1,Samsung Electro-Mechanics,CL21A475KOFNNNG,"4.7 uF, 16 V, 10%, X5R MLCC",0805 (2012 Metric); Capacitor_SMD:C_0805_2012Metric,C16194928,SMT,https://www.lcsc.com/product-detail/C16194928.html,
Y1,1,YXC,X322516MOB4SI,"16 MHz, 12 pF load crystal",SMD3225-4P; Crystal:Crystal_SMD_3225-4Pin_3.2x2.5mm,C12668,SMT,https://www.lcsc.com/product-detail/C12668.html,12 pF load is consistent with two 15 pF capacitors plus estimated pin and PCB stray capacitance; verify oscillator margin on prototypes.
SW1,1,C&K,RS-282G05A3-SMRT,Momentary SPST reset switch,C&K RS-282G05A3 SMD; Button_Switch_SMD:SW_SPST_CK_RS282G05A3,C221930,SMT,https://www.lcsc.com/product-detail/C221930.html,
J1,1,XFCN,PZ254V-11-12P,Single-row male pin header,"1x12, 2.54 mm pitch, vertical THT; Connector_PinHeader_2.54mm:PinHeader_1x12_P2.54mm_Vertical",C2840012,THT,https://www.lcsc.com/product-detail/C2840012.html,Quote THT assembly separately and confirm pin protrusion suits breadboards.
